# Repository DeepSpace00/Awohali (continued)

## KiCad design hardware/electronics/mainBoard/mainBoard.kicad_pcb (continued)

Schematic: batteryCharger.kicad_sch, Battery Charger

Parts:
C90, C93, C94, C98, C99: 100nF; GCM0402; Tolerance 10%; Voltage Rating 50V; MPN GRT155R71H104KE01D
C91, C92, C95, C96, C97, C100, C101, C102, C103, C104, C106, C107: 10uF; GRT1210; Tolerance 10%; Voltage Rating 25V; MPN GCM32ER71E106KA57L
C105, C108, C109: 47nF; GCM0402; Tolerance 10%; Voltage Rating 25V; MPN GRT155R71E473KE01D
C110: 4.7uF; GCM0805; Tolerance 10%; Voltage Rating 16V; MPN GRT21BR71C475KE13L
D5: PTVS13VS1UR; SOD123W; Voltage - Reverse Stabd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 13V; Voltage - Breakdown 14V4; MPN PTVS13VS1UR,115
D6, D8: ESD321DYAR; SOD523; Voltage - Reverse Stabd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 3V6; Voltage - Breakdown 4V5; MPN ESD321DYAR
D9: TPD1E05U06-Q1; SON2P65_100X60X50L50X25N; Voltage - Reverse Stabd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 5V5; Voltage - Breakdown 6V4; MPN TPD1E05U06QDPYRQ1
D15, D16: BZT52C12T-7; SOD523; Zener Voltage 12V; Forward Voltage 900mV; MPN BZT52C12T-7
D17: LTST-C191KGKT; LTST-0603; Forward Voltage 2V; MPN LTST-C191KGKT
J25: M8AS-02PFFR-SF8001; MPN M8AS-02PFFR-SF8001
J26: MUSBRM1C1M0; MUSBR-M1C1-XX; MPN MUSBRM1C1M0
J27: S2B-PH-SM4-TB; JST-PH-S2B-SM4-TB; MPN S2B-PH-SM4-TB
JP10: SolderJumper-2_P1.3mm_Bridged_RoundedPad1.0x1.5mm
L6: 2.2uH; WE-XHMI-4030; Tolerance 20%; Current Rating 7A8; MPN 74439324022
NT7, NT8: NetTie; NetTie-2_SMD_Pad2.0mm
Q1, Q3, Q4: CSD17581Q3A; SON65P300X315X90-8; MPN Texas Instruments
Q2, Q5: CSD17581Q3A; SON65P300X315X90-8; MPN CSD17581Q3A
R61: 294R; CRCW0402; Tolerance 1%; Power Rating 62m5W; MPN CRCW0402294RFKED
R62: 8K2; CRCW0402; Tolerance 1%; Power Rating 62m5W; MPN CRCW04028K20FKED
R63: 294R; CRCW0402; Tolerance 1%; Power Rating 62m5W; MPN CRCW04026K04FKED
R64, R65, R70: 5K1; CRCW0402; Tolerance 1%; Power Rating 62m5W; MPN CRCW04025K10FKED
R66: 100R; CRCW0402; Tolerance 5%; Power Rating 62m5W; MPN CRCW0402100RJNED
R67: 2K2; CRCW0402; Tolerance 1%; Power Rating 62m5W; MPN CRCW04022K20FKED
R68: 10K; CRCW0402; Tolerance 1%; Power Rating 62m5W; MPN CRCW040210K0FKED
R69: 187K; CRCW0402; Tolerance 1%; Power Rating 62m5W; MPN CRCW0402187KFKED
R71: 100K; CRCW0402; Tolerance 1%; Power Rating 62m5W; MPN CRCW0402100KFKED
R72: 29K4; CRCW0402; Tolerance 1%; Power Rating 62m5W; MPN CRCW040229K4FKED
TP77, TP78, TP80, TP81, TP83, TP85, TP86, TP88, TP89: TP_2mm; MPN N/A
TP79, TP82, TP84, TP87, TP90: RCWCTE; TP_RCW; MPN RCWCTE
U20: BQ25798; QFN40P400X400X100-29; MPN BQ25798RQMR

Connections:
+3V3: R68.1; also elsewhere on the board
/EPS Controller/BAT_CHG_INT: R68.2, U20.21 (~INT); also elsewhere on the board
/EPS Controller/Battery Charger/ACDRV1: R63.2, TP83.1, U20.11 (ACDRV1)
/EPS Controller/Battery Charger/ACDRV2: R61.2, TP85.1, U20.10 (ACDRV2)
/EPS Controller/Battery Charger/BAT: C106.1, C107.1, Q5.1, Q5.2, Q5.3, U20.22 (BAT), U20.23 (BAT)
/EPS Controller/Battery Charger/BATP: C109.1, R66.1, U20.18 (BATP)
/EPS Controller/Battery Charger/BTST1: C105.1, U20.4 (BTST1)
/EPS Controller/Battery Charger/BTST2: C108.2, U20.19 (BTST2)
/EPS Controller/Battery Charger/CC1: J26.A5 (CC1), R64.1
/EPS Controller/Battery Charger/CC2: J26.B5 (CC2), R65.1
/EPS Controller/Battery Charger/ILIM_HZ: R69.2, R71.1, U20.17 (ILIM_HZ)
/EPS Controller/Battery Charger/PMID: C94.1, C95.1, C96.1, C97.1, U20.29 (PMID)
/EPS Controller/Battery Charger/PROG: R62.1, U20.20 (PROG)
/EPS Controller/Battery Charger/PVIN: C90.1, D5.1, J25.1 (VDD), Q1.5, Q1.6, Q1.7, Q1.8, Q1.9, TP89.1, U20.8 (VAC2)
/EPS Controller/Battery Charger/REGN: C110.1, JP10.1, R69.1, R70.1, U20.5 (REGN)
/EPS Controller/Battery Charger/SDRV: Q5.4, U20.24 (SDRV)
/EPS Controller/Battery Charger/SW1: C105.2, L6.1, U20.28 (SW1)
/EPS Controller/Battery Charger/SW2: C108.1, L6.2, U20.26 (SW2)
/EPS Controller/Battery Charger/VCHG: C91.1, C92.1, C93.1, Q2.5, Q2.6, Q2.7, Q2.8, Q2.9, Q4.5, Q4.6, Q4.7, Q4.8, Q4.9, TP81.1, U20.2 (VBUS), U20.3 (VBUS)
/EPS Controller/TS: J27.1, R70.2, R72.1, U20.16 (TS); also elsewhere on the board
/EPS Controller/USB_FS.DN: D8.1, J26.A7 (D1-), J26.B7 (D2-), TP88.1; also elsewhere on the board
/EPS Controller/USB_FS.DP: D6.1, J26.A6 (D1+), J26.B6 (D2+), TP86.1; also elsewhere on the board
/EPS Controller/~CE: U20.13 (~CE); also elsewhere on the board
/EPS Controller/~QON: U20.12 (~QON); also elsewhere on the board
/EPS.SCL: U20.14 (SCL); also elsewhere on the board
/EPS.SDA: U20.15 (SDA); also elsewhere on the board
AGND: C90.2, C98.2, J27.2, NT7.2, R62.2, R71.2, R72.2, TP84.1; also elsewhere on the board
CHG+: Q5.5, Q5.6, Q5.7, Q5.8, Q5.9, R66.2, TP80.1; also elsewhere on the board
CHG-: C106.2, C107.2, TP87.1; also elsewhere on the board
GND: C91.2, C92.2, C93.2, C94.2, C95.2, C96.2, C97.2, C99.2, C100.2, C101.2, C102.2, C103.2, C104.2, C109.2, C110.2, D5.2, D6.2, D8.2, D9.2, J25.2 (VSS), J25.S1 (SHIELD), J25.S2 (SHIELD), J26.A1 (GND), J26.A12 (GND), J26.B1 (GND), J26.B12 (GND), J26.G1 (GND), J26.G2 (GND), J26.G3 (GND), J26.G4 (GND), J26.G5 (GND), J26.G6 (GND), J26.S1, J26.S2, NT7.1, NT8.1, R64.2, R65.2, TP79.1, TP82.1, TP90.1, U20.27 (GND); also elsewhere on the board
unnamed: D15.1, Q1.1, Q1.2, Q1.3, Q2.1, Q2.2, Q2.3
unnamed: D15.2, Q1.4, Q2.4, R61.1
unnamed: D16.1, Q3.1, Q3.2, Q3.3, Q4.1, Q4.2, Q4.3
unnamed: D16.2, Q3.4, Q4.4, R63.1
unnamed: D17.1, R67.2
unnamed: JP10.2, R67.1
unnamed: D17.2, U20.1 (STAT)
VBUS: C98.1, D9.1, J26.A4 (VBUS), J26.A9 (VBUS), J26.B4 (VBUS), J26.B9 (VBUS), Q3.5, Q3.6, Q3.7, Q3.8, Q3.9, TP77.1, U20.9 (VAC1)
VSS: NT8.2; also elsewhere on the board
VSYS: C99.1, C100.1, C101.1, C102.1, C103.1, C104.1, TP78.1, U20.25 (SYS); also elsewhere on the board

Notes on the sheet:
Upstream Facing USB Port
VIN: 12V
VIN: 5V@3A
I2C Address: 0x6B
Pv Panel Jack
Thermistor Connector
Pull ~{QON} low to activate shutdown mode
Charge Enable: Pull ~{CE} LOW Charge Disable: Pull ~{CE} HIGH
10K NTC
Battery Charger
Prog Resistor: 6K04 - 2S @ 1500kHz 8K2 - 2S @ 750kHz 10K5 - 3S @ 1500kHz 13K7 - 3S @ 750kHz
R69 = (RTH_COLD * RTH_HOT * (1/VT1 - 1/VT5)) / (RTH_HOT * (1/VT5 - 1) - RTH_COLD * (1/VT1 - 1)) R67 = (1/VT1 - 1) / (1/R208 + 1/RTH_COLD)
V_ILIM_HIZ = 1V + 800mR * I_INDPM I_INDPM (target input current) = 4A V_ILIM_HIZ = 4200mV R66 = R167(12000mV - 4200mV)/4200mV R68 = 100K R66 ~= 187K

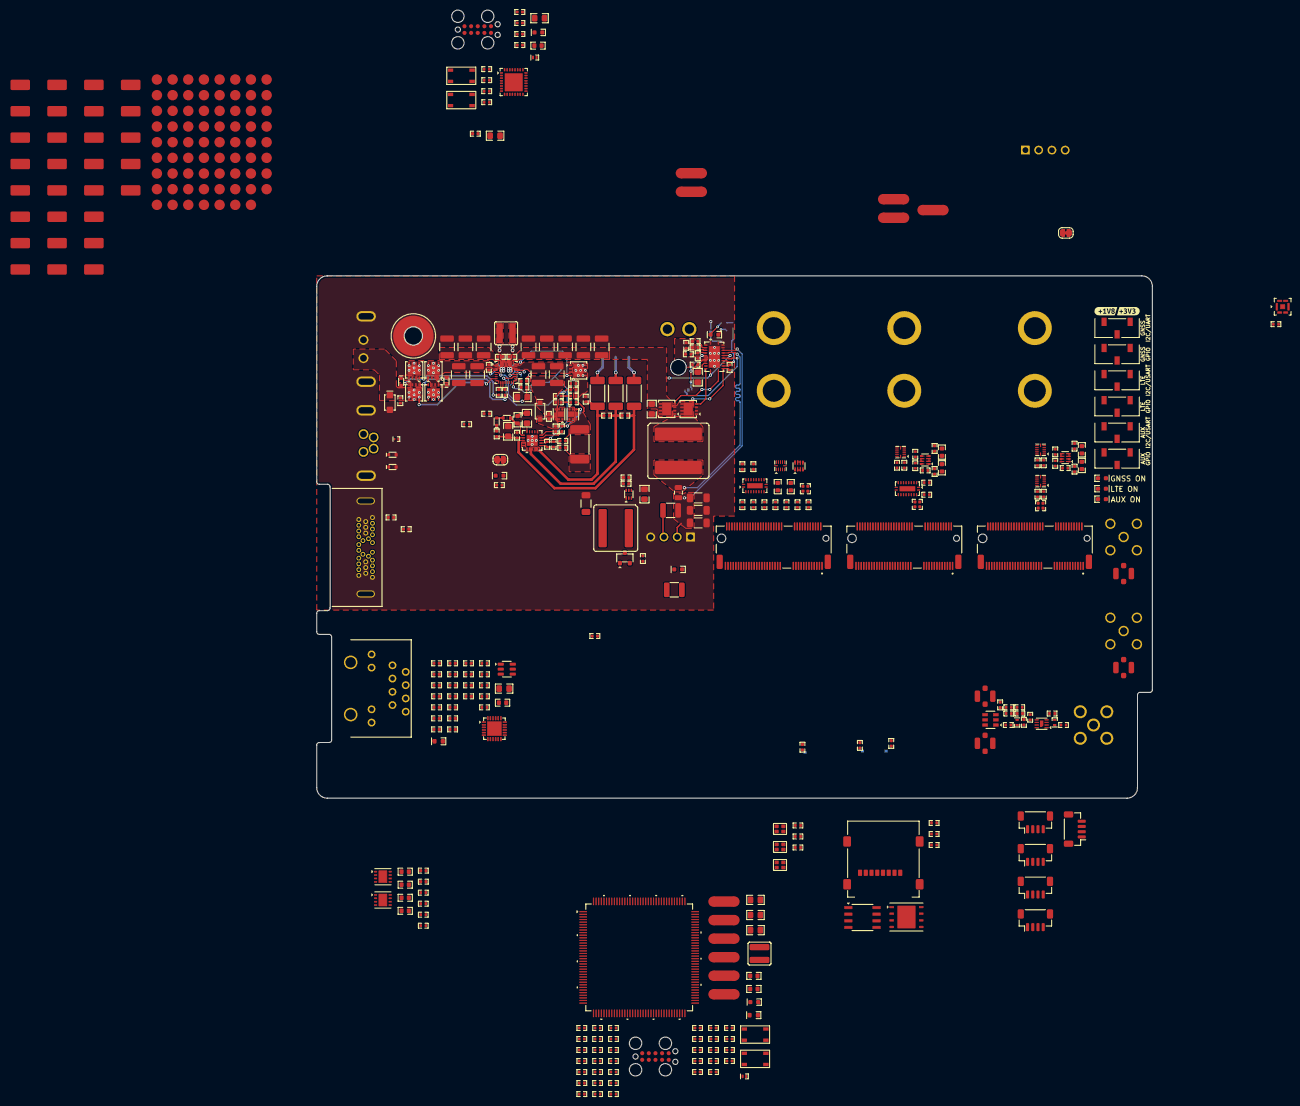
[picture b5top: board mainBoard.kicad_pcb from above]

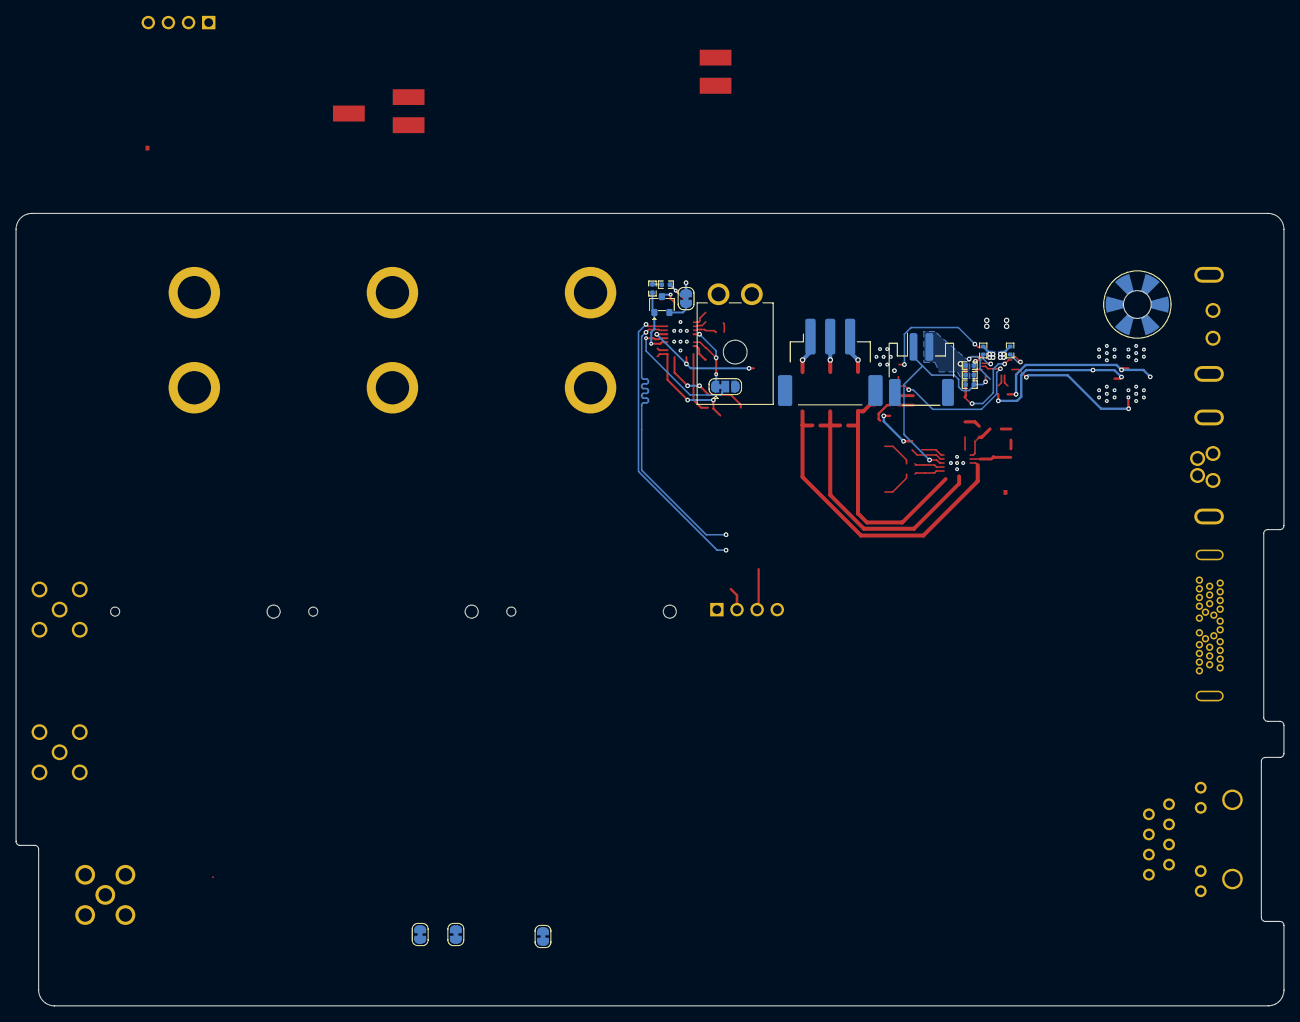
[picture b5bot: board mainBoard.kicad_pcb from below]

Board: 4 copper layers, 160.0 x 100.0 mm, 451 parts (16 on the bottom side), 272 nets.

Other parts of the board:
kibuzzard-67E082B6: G***; kibuzzard-67E082B6
kibuzzard-67E082BE: G***; kibuzzard-67E082BE

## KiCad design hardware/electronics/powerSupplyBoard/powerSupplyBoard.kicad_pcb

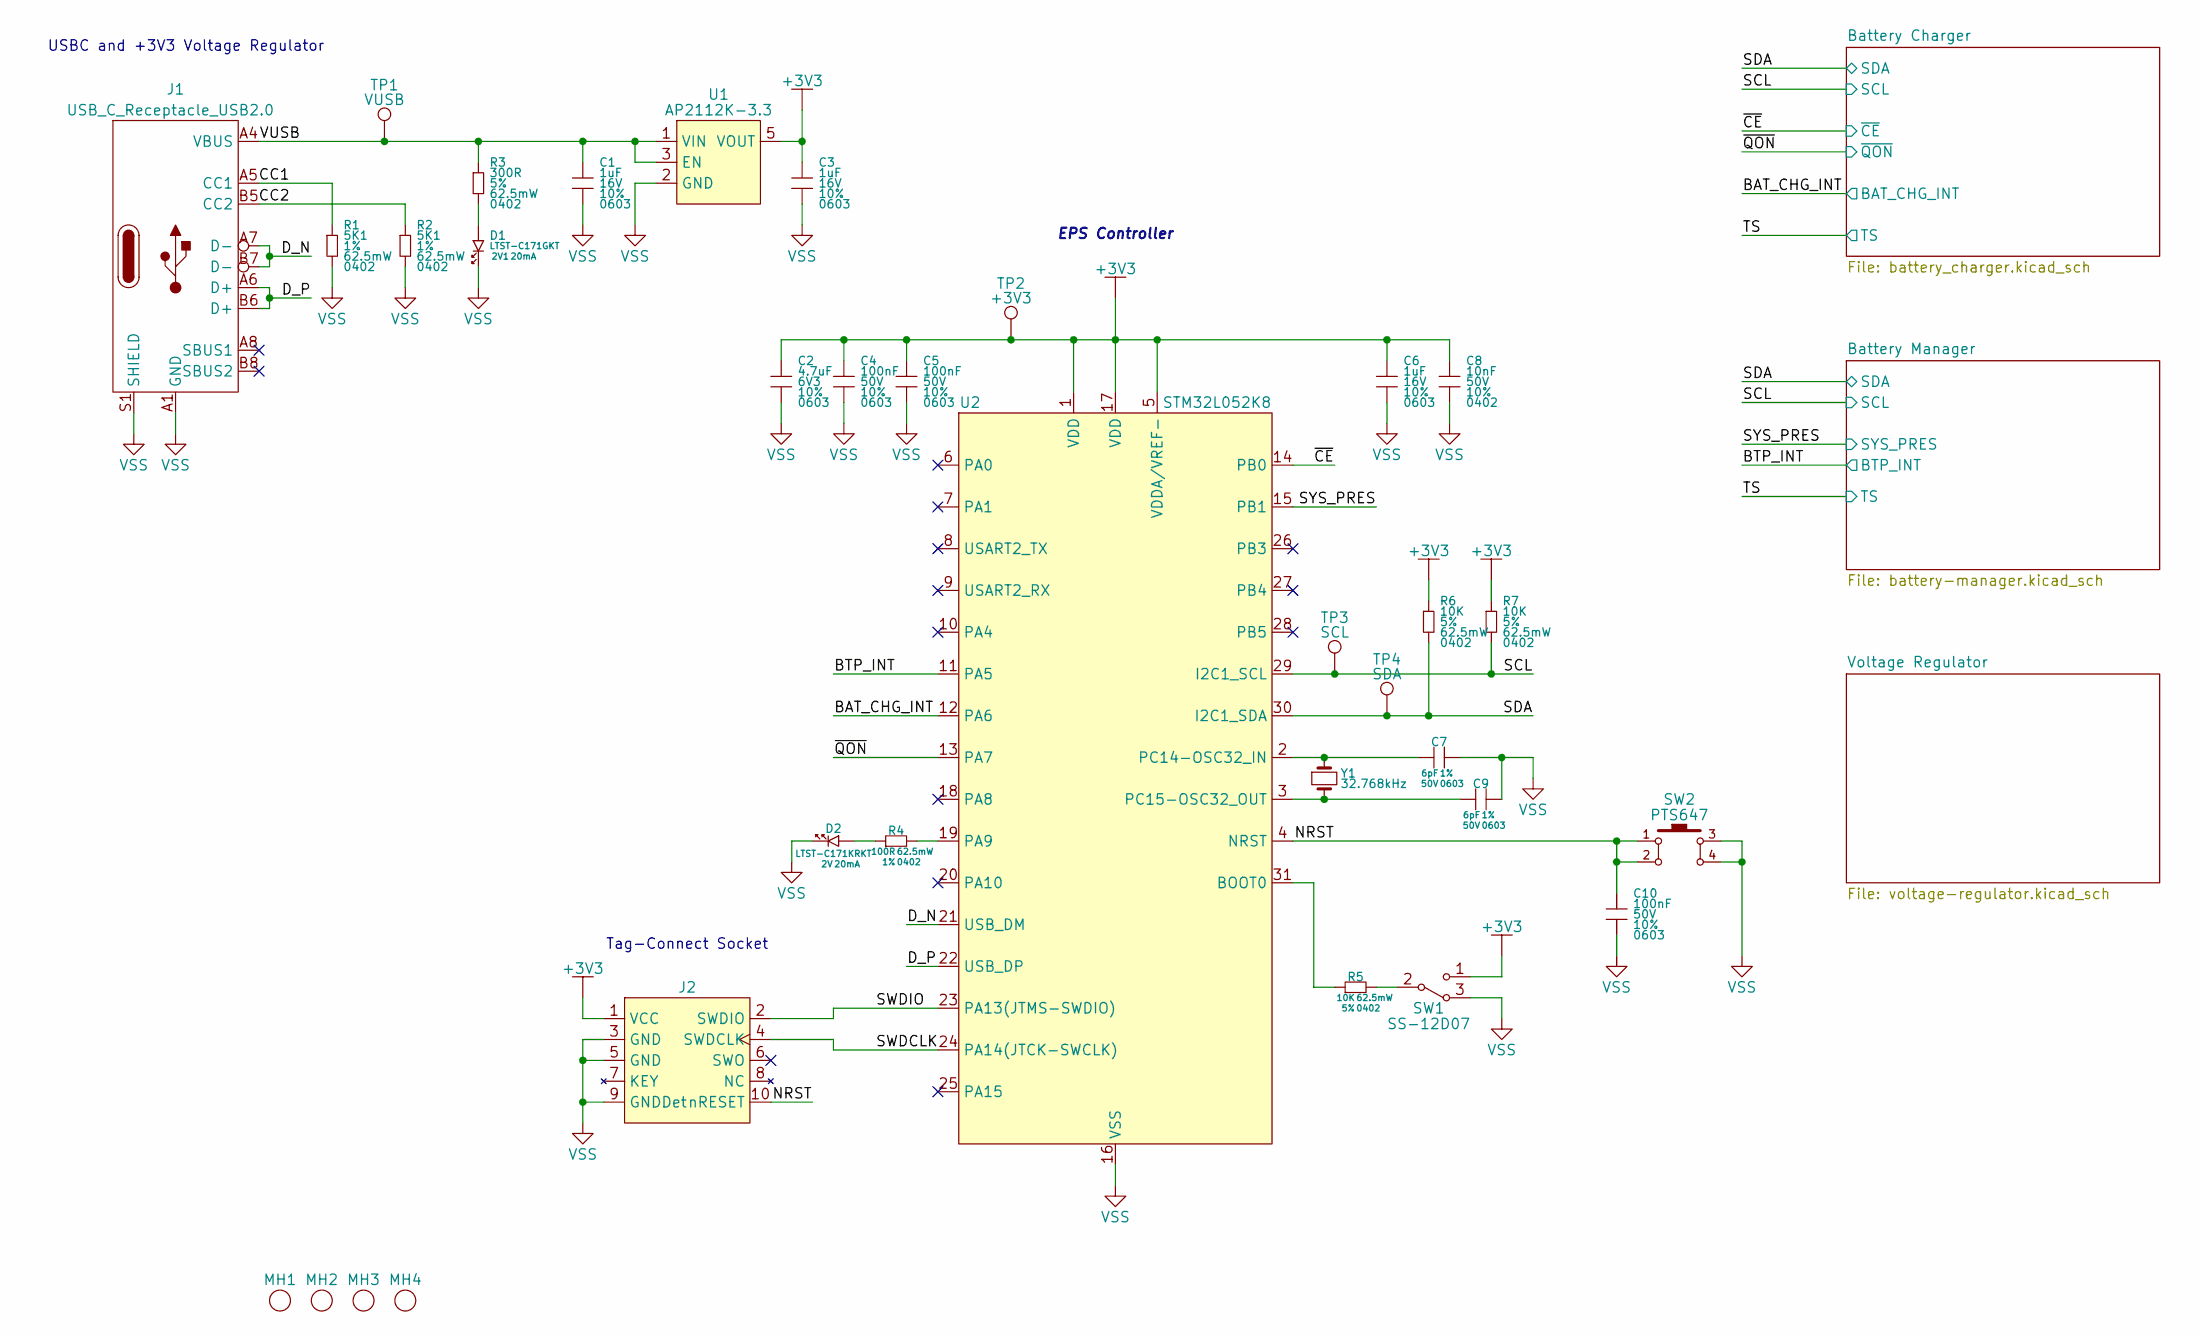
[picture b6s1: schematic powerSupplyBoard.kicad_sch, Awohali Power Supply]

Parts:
C1, C3, C6: 1uF; MLCC0603; Tolerance 10%; Voltage Rating 16V; MPN KAM15AR71C105KT
C2: 4.7uF; MLCC0603; Tolerance 10%; Voltage Rating 6V3; MPN KAM15CR70J475KT
C4, C5, C10: 100nF; MLCC0603; Tolerance 10%; Voltage Rating 50V; MPN KAM15AR71H104KM
C7, C9: 6pF; MLCC0603; Tolerace 1%; Voltage Rating 50V; MPN 06035A6R0B4T2A
C8: 10nF; MLCC0402; Tolerance 10%; Voltage Rating 50V; MPN KAM05AR71H103KH
D1: LTST-C171GKT; LTST-0805; Forward Voltage 2V1; MPN LTST-C171GKT
D2: LTST-C171KRKT; LTST-0805; Forward Voltage 2V; MPN LTST-C171KRKT
J1: USB_C_Receptacle_USB2.0; MOLEX_2171790001
J2: TC2050-FP; MPN N/A
MH1, MH2, MH3, MH4: M3_NPTH
R1, R2: 5K1; CRCW0402; Tolerance 1%; Power Rating 62.5mW; MPN CRCW04025K10FKED
R3: 300R; CRCW0402; Tolerance 5%; Power Rating 62.5mW; MPN CRCW0402300RJNED
R4: 100R; CRCW0402; Tolerance 1%; Power Rating 62.5mW; MPN CRCW0402100RFKED
R5, R6, R7: 10K; CRCW0402; Tolerance 5%; Power Rating 62.5mW; MPN CRCW040210K0JNED
SW1: SS-12D07; SS-12D07-VG_GA_PA; MPN SS-12D07-VG 4 NS GA PA
SW2: PTS647; SW_4.5x4.5; MPN PTS 647 SK38 SMTR2 LFS
TP1: VUSB; TP_1mm
TP2: +3V3; TP_1mm
TP3: SCL; TP_1mm
TP4: SDA; TP_1mm
U1: AP2112K-3.3; SOT23-5P95_280X300X110L40X38N; MPN AP2112K-3.3TRG1
U2: STM32L052K8; UFQFPN32; MPN STM32L052K8U6TR
Y1: ECS-327ATQMV; EXC-34Q; MPN ECS-.327-6-34QS-TR

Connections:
+3V3: C2.1, C3.1, C4.1, C5.1, C6.1, C8.1, J2.1 (VCC), R6.1, R7.1, SW1.1, TP2.1, U1.5 (VOUT), U2.1 (VDD), U2.5 (VDDA/VREF-), U2.17 (VDD); also elsewhere on the board
/BAT_CHG_INT: U2.12 (PA6); also elsewhere on the board
/BTP_INT: U2.11 (PA5); also elsewhere on the board
/CC1: J1.A5 (CC1), R1.1
/CC2: J1.B5 (CC2), R2.1
/D_N: J1.A7 (D-), J1.B7 (D-), U2.21 (USB_DM)
/D_P: J1.A6 (D+), J1.B6 (D+), U2.22 (USB_DP)
/NRST: C10.1, J2.10 (nRESET), SW2.1, SW2.2, U2.4 (NRST)
/SCL: R7.2, TP3.1, U2.29 (I2C1_SCL); also elsewhere on the board
/SDA: R6.2, TP4.1, U2.30 (I2C1_SDA); also elsewhere on the board
/SWDCLK: J2.4 (SWDCLK), U2.24 (PA14(JTCK-SWCLK))
/SWDIO: J2.2 (SWDIO), U2.23 (PA13(JTMS-SWDIO))
/SYS_PRES: U2.15 (PB1); also elsewhere on the board
/VUSB: C1.1, J1.A4 (VBUS), J1.A9 (VBUS), J1.B4 (VBUS), J1.B9 (VBUS), R3.1, TP1.1, U1.1 (VIN), U1.3 (EN)
/~CE: U2.14 (PB0); also elsewhere on the board
/~QON: U2.13 (PA7); also elsewhere on the board
unnamed: D1.1, R3.2
unnamed: D2.1, R4.1
unnamed: R5.2, SW1.2
unnamed: R5.1, U2.31 (BOOT0)
unnamed: R4.2, U2.19 (PA9)
unnamed: C7.1, U2.2 (PC14-OSC32_IN), Y1.1
unnamed: C9.1, U2.3 (PC15-OSC32_OUT), Y1.2
VSS: C1.2, C2.2, C3.2, C4.2, C5.2, C6.2, C7.2, C8.2, C9.2, C10.2, D1.2, D2.2, J1.A1 (GND), J1.A12 (GND), J1.B1 (GND), J1.B12 (GND), J1.S1 (SHIELD), J2.3 (GND), J2.5 (GND), J2.9 (GNDDet), R1.2, R2.2, SW1.3, SW2.3, SW2.4, U1.2 (GND), U2.16 (VSS), U2.32 (VSS), U2.33 (VSS); also elsewhere on the board

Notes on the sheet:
Tag-Connect Socket
EPS Controller
USBC and +3V3 Voltage Regulator

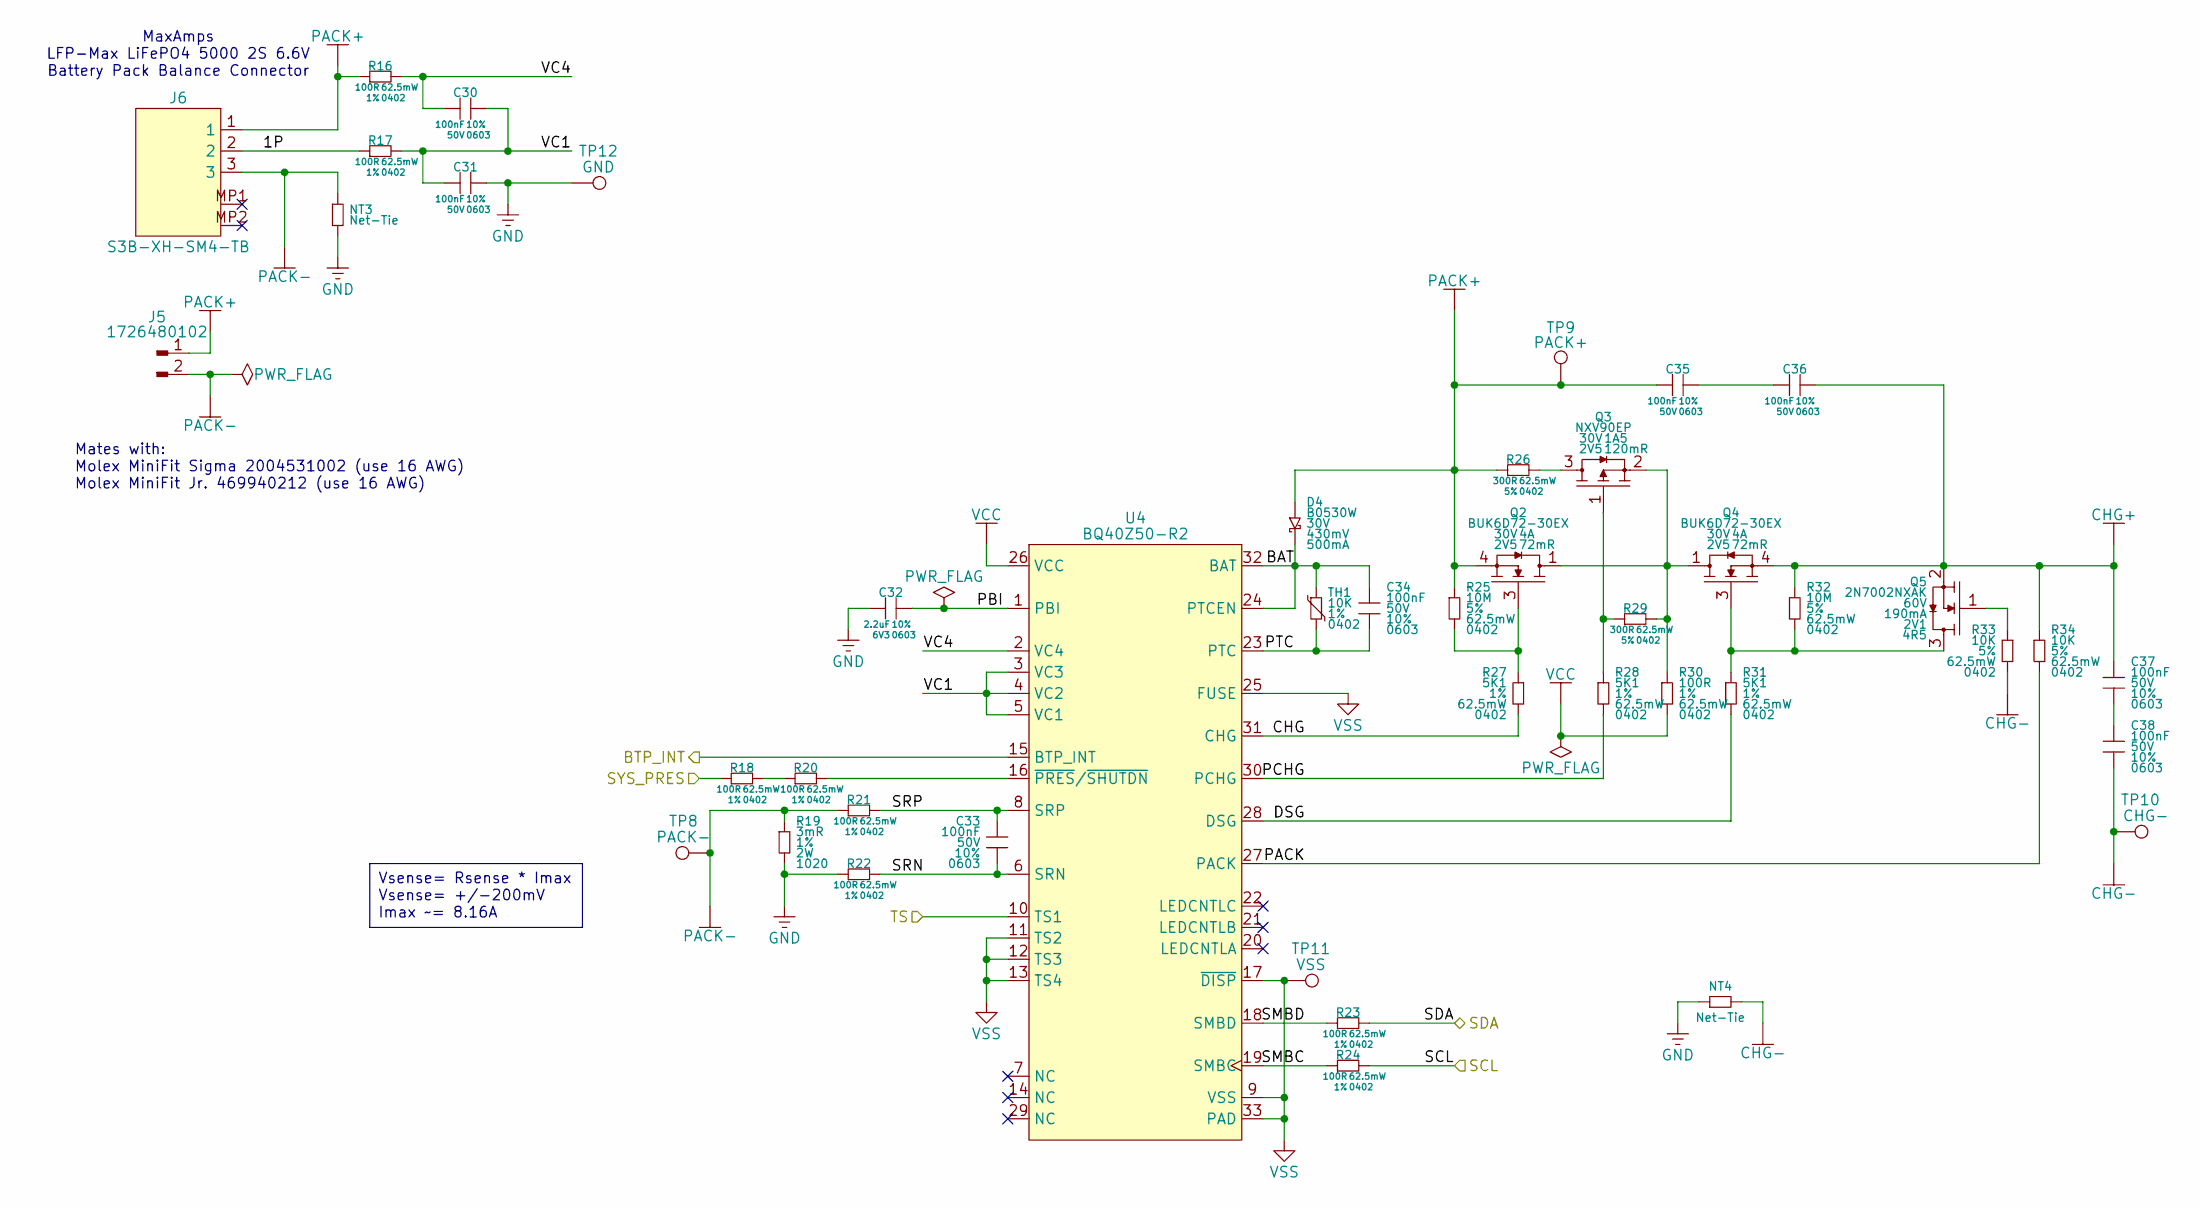
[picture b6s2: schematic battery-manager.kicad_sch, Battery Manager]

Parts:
C30, C31, C35, C36: 100nF; MLCC0603; Tolerace 10%; Voltage Rating 50V; MPN KAM15AR71H104KM
C32: 2.2uF; MLCC0603; Tolerace 10%; Voltage Rating 6V3; MPN KAM15AR70J225KT
C33, C34, C37, C38: 100nF; MLCC0603; Tolerance 10%; Voltage Rating 50V; MPN KAM15AR71H104KM
D4: B0530W; SOD123; Reverse Voltage 30V; Forward Voltage 430mV; MPN B0530W-7-F
J5: 1726480102; MPN 1726480102
J6: S3B-XH-SM4-TB; JST_XH_S3B-SM4-TB; MPN S3B-XH-SM4-TB
NT3, NT4: Net-Tie; NetTie-2_SMD_Pad2.0mm
Q2, Q4: BUK6D72-30EX; UDFN6P65_200X200X65L30X25N; MPN BUK6D72-30EX
Q3: NXV90EP; SOT23-3P95_230X290X100L43X30N; MPN NXV90EPR
Q5: 2N7002NXAK; SOT23-3P95_230X290X100L43X30N; MPN 2N7002NXAKR
R16, R17, R18, R20, R21, R22, R23, R24, R30: 100R; CRCW0402; Tolerance 1%; Power Rating 62.5mW; MPN CRCW0402100RFKED
R19: 3mR; WSL1020; Tolerance 1%; Power Rating 2W; MPN WSL10203L000FEA
R25, R32: 10M; CRCW0402; Tolerance 5%; Power Rating 62.5mW; MPN CRCW040210M0JNED
R26, R29: 300R; CRCW0402; Tolerance 5%; Power Rating 62.5mW; MPN CRCW0402300RJNED
R27, R28, R31: 5K1; CRCW0402; Tolerance 1%; Power Rating 62.5mW; MPN CRCW04025K10FKED
R33, R34: 10K; CRCW0402; Tolerance 5%; Power Rating 62.5mW; MPN CRCW040210K0JNED
TH1: 10K; SON2P65_100X60X50L50X25N; Resistance Tolerance 1%; MPN TMP6131QDECRQ1
TP8: PACK-; TP_1mm
TP9: PACK+; TP_1mm
TP10: CHG-; TP_1mm
TP11: VSS; TP_1mm
TP12: GND; TP_1mm
U4: BQ40Z50-R2; RSM0032A; MPN BQ40Z50RSMR-R2

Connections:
/BTP_INT: U4.15 (BTP_INT); also elsewhere on the board
/Battery Manager/1P: J6.2, R17.1
/Battery Manager/BAT: C34.1, D4.2, TH1.1, U4.24 (PTCEN), U4.32 (BAT)
/Battery Manager/CHG: R27.2, U4.31 (CHG)
/Battery Manager/DSG: R31.2, U4.28 (DSG)
/Battery Manager/PACK: R34.2, U4.27 (PACK)
/Battery Manager/PBI: C32.2, U4.1 (PBI)
/Battery Manager/PCHG: R28.2, U4.30 (PCHG)
/Battery Manager/PTC: C34.2, TH1.2, U4.23 (PTC)
/Battery Manager/SMBC: R24.1, U4.19 (SMBC)
/Battery Manager/SMBD: R23.1, U4.18 (SMBD)
/Battery Manager/SRN: C33.2, R22.2, U4.6 (SRN)
/Battery Manager/SRP: C33.1, R21.2, U4.8 (SRP)
/Battery Manager/VC1: C30.2, C31.1, R17.2, U4.3 (VC3), U4.4 (VC2), U4.5 (VC1)
/Battery Manager/VC4: C30.1, R16.2, U4.2 (VC4)
/SCL: R24.2; also elsewhere on the board
/SDA: R23.2; also elsewhere on the board
/SYS_PRES: R18.1; also elsewhere on the board
/TS: U4.10 (TS1); also elsewhere on the board
CHG+: C36.2, C37.1, Q4.4, Q4.8, Q5.2, R32.1, R34.1; also elsewhere on the board
CHG-: C38.2, NT4.2, R33.2, TP10.1; also elsewhere on the board
GND: C31.2, C32.1, NT3.2, NT4.1, R19.2, R22.1, TP12.1; also elsewhere on the board
unnamed: C35.2, C36.1
unnamed: C37.2, C38.1
unnamed: Q2.1, Q2.2, Q2.5, Q2.6, Q2.7, Q3.2, Q4.1, Q4.2, Q4.5, Q4.6, Q4.7, R29.2, R30.1
unnamed: Q2.3, R25.2, R27.1
unnamed: Q3.1, R28.1, R29.1
unnamed: Q3.3, R26.2
unnamed: Q4.3, Q5.3, R31.1, R32.2
unnamed: Q5.1, R33.1
unnamed: R18.2, R20.1
unnamed: R20.2, U4.16 (~PRES/~SHUTDN)
PACK+: C35.1, D4.1, J5.1, J6.1, Q2.4, Q2.8, R16.1, R25.1, R26.1, TP9.1
PACK-: J5.2, J6.3, NT3.1, R19.1, R21.1, TP8.1
VCC: R30.2, U4.26 (VCC)
VSS: TP11.1, U4.9 (VSS), U4.11 (TS2), U4.12 (TS3), U4.13 (TS4), U4.17 (~DISP), U4.25 (FUSE), U4.33 (PAD); also elsewhere on the board

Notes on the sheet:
MaxAmps LFP-Max LiFePO4 5000 2S 6.6V Battery Pack Balance Connector
Mates with: Molex MiniFit Sigma 2004531002 (use 16 AWG) Molex MiniFit Jr. 469940212 (use 16 AWG)
Vsense= Rsense * Imax Vsense= +/-200mV Imax ~= 8.16A

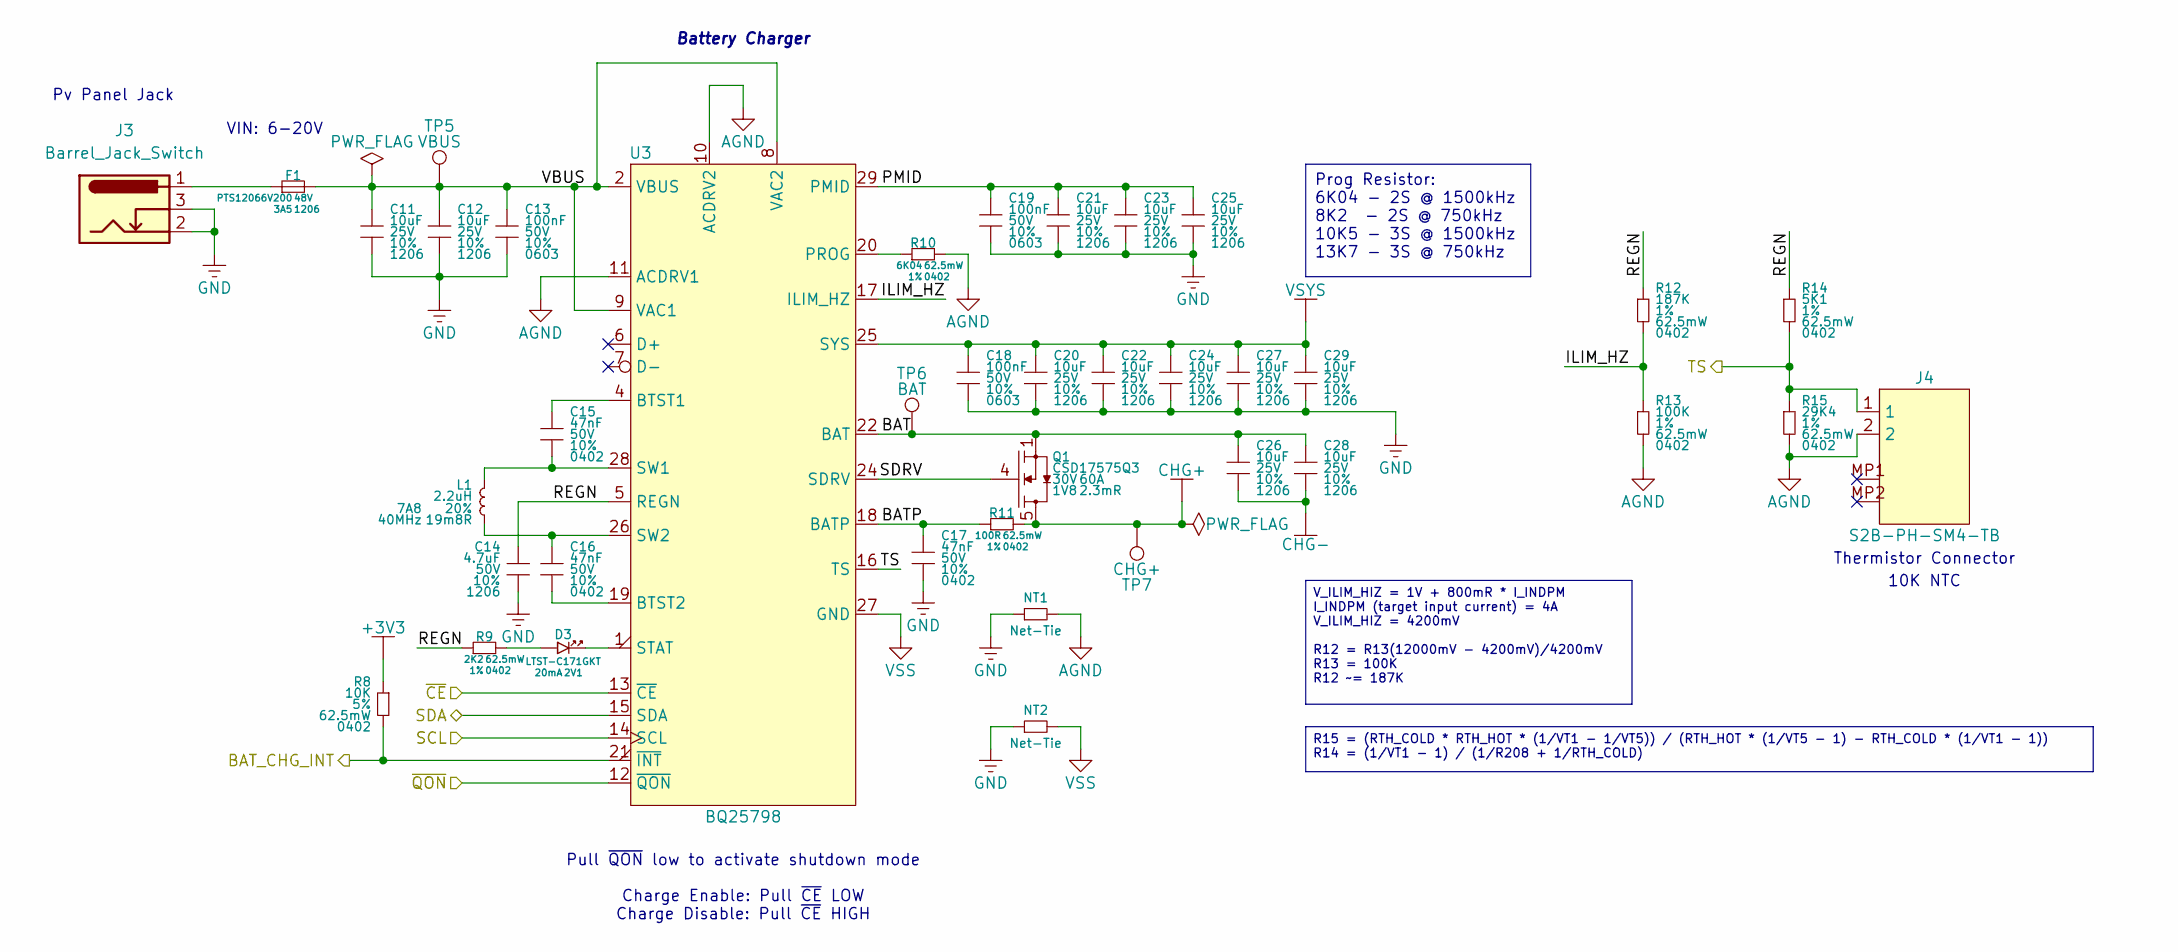
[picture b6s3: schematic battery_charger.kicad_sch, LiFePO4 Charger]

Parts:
C11, C12, C20, C21, C22, C23, C24, C25, C26, C27, C28, C29: 10uF; MLCC1206; Tolerance 10%; Voltage Rating 25V; MPN CGA5L1X7R1E106K160DC
C13, C18, C19: 100nF; MLCC0603; Tolerance 10%; Voltage Rating 50V; MPN KAM15AR71H104KM
C14: 4.7uF; MLCC1206; Tolerance 10%; Voltage Rating 50V; MPN 12065C475K4T4A
C15, C16, C17: 47nF; MLCC0402; Tolerance 10%; Voltage Rating 50V; MPN 04025C472K4T2A
D3: LTST-C171GKT; LTST-0805; Forward Voltage 2V1; MPN LTST-C171GKT
F1: PTS12066V200; PTS1206; Voltage 48V; MPN PTS12066V200
J3: Barrel_Jack_Switch; PJ-002A; MPN PJ-002A
J4: S2B-PH-SM4-TB; JST-PH-S2B-SM4-TB; MPN S2B-PH-SM4-TB
L1: 2.2uH; WE-XHMI-4030; Tolerance 20%; Current Rating 7A8; MPN 74439324022
NT1, NT2: Net-Tie; NetTie-2_SMD_Pad2.0mm
Q1: CSD17575Q3; SON8P65_330X330X100L45X34N; MPN CSD17575Q3
R8: 10K; CRCW0402; Tolerance 5%; Power Rating 62.5mW; MPN CRCW040210K0JNED
R9: 2K2; CRCW0402; Tolerance 1%; Power Rating 62.5mW; MPN CRCW04022K20FKED
R10: 6K04; CRCW0402; Tolerance 1%; Power Rating 62.5mW; MPN CRCW04026K04FKED
R11: 100R; CRCW0402; Tolerance 1%; Power Rating 62.5mW; MPN CRCW0402100RFKED
R12: 187K; CRCW0402; Tolerance 1%; Power Rating 62.5mW; MPN CRCW0402187KFKED
R13: 100K; CRCW0402; Tolerance 1%; Power Rating 62.5mW; MPN CRCW0402100KFKED
R14: 5K1; CRCW0402; Tolerance 1%; Power Rating 62.5mW; MPN CRCW04025K10FKED
R15: 29K4; CRCW0402; Tolerance 1%; Power Rating 62.5mW; MPN CRCW040229K4FKED
TP5: VBUS; TP_1mm
TP6: BAT; TP_1mm
TP7: CHG+; TP_1mm
U3: BQ25798; RQM0029A; MPN BQ25798

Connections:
+3V3: R8.1; also elsewhere on the board
/BAT_CHG_INT: R8.2, U3.21 (~INT); also elsewhere on the board
/Battery Charger/BAT: C26.1, C28.1, Q1.1, Q1.2, Q1.3, TP6.1, U3.22 (BAT), U3.23 (BAT)
/Battery Charger/BATP: C17.1, R11.1, U3.18 (BATP)
/Battery Charger/ILIM_HZ: R12.2, R13.1, U3.17 (ILIM_HZ)
/Battery Charger/PMID: C19.1, C21.1, C23.1, C25.1, U3.29 (PMID)
/Battery Charger/REGN: C14.1, R9.1, R12.1, R14.1, U3.5 (REGN)
/Battery Charger/SDRV: Q1.4, U3.24 (SDRV)
/SCL: U3.14 (SCL); also elsewhere on the board
/SDA: U3.15 (SDA); also elsewhere on the board
/TS: J4.1, R14.2, R15.1, U3.16 (TS); also elsewhere on the board
/~CE: U3.13 (~CE); also elsewhere on the board
/~QON: U3.12 (~QON); also elsewhere on the board
AGND: J4.2, NT1.2, R10.2, R13.2, R15.2, U3.10 (ACDRV2), U3.11 (ACDRV1)
CHG+: Q1.5, Q1.6, Q1.7, Q1.8, R11.2, TP7.1; also elsewhere on the board
CHG-: C26.2, C28.2; also elsewhere on the board
GND: C11.2, C12.2, C13.2, C14.2, C17.2, C18.2, C19.2, C20.2, C21.2, C22.2, C23.2, C24.2, C25.2, C27.2, C29.2, J3.2, J3.3, NT1.1, NT2.1; also elsewhere on the board
unnamed: D3.1, R9.2
unnamed: F1.1, J3.1
unnamed: C15.1, U3.4 (BTST1)
unnamed: C16.2, U3.19 (BTST2)
unnamed: R10.1, U3.20 (PROG)
unnamed: D3.2, U3.1 (STAT)
unnamed: C15.2, L1.1, U3.28 (SW1)
unnamed: C16.1, L1.2, U3.26 (SW2)
VBUS: C11.1, C12.1, C13.1, F1.2, TP5.1, U3.2 (VBUS), U3.3 (VBUS), U3.8 (VAC2), U3.9 (VAC1)
VSS: NT2.2, U3.27 (GND); also elsewhere on the board
VSYS: C18.1, C20.1, C22.1, C24.1, C27.1, C29.1, U3.25 (SYS); also elsewhere on the board

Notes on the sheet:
Pv Panel Jack
VIN: 6-20V
Battery Charger
10K NTC
Charge Enable: Pull ~{CE} LOW Charge Disable: Pull ~{CE} HIGH
Pull ~{QON} low to activate shutdown mode
Thermistor Connector
V_ILIM_HIZ = 1V + 800mR * I_INDPM I_INDPM (target input current) = 4A V_ILIM_HIZ = 4200mV R12 = R13(12000mV - 4200mV)/4200mV R13 = 100K R12 ~= 187K
Prog Resistor: 6K04 - 2S @ 1500kHz 8K2 - 2S @ 750kHz 10K5 - 3S @ 1500kHz 13K7 - 3S @ 750kHz
R15 = (RTH_COLD * RTH_HOT * (1/VT1 - 1/VT5)) / (RTH_HOT * (1/VT5 - 1) - RTH_COLD * (1/VT1 - 1)) R14 = (1/VT1 - 1) / (1/R208 + 1/RTH_COLD)

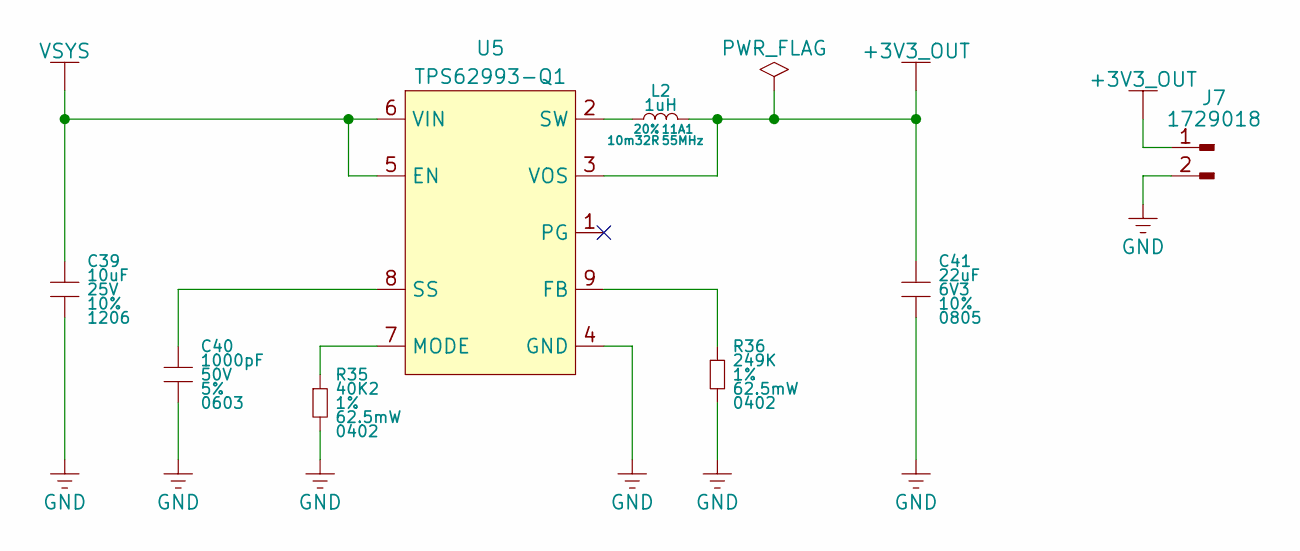
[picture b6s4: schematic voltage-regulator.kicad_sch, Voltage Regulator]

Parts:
C39: 10uF; MLCC1206; Tolerance 10%; Voltage Rating 25V; MPN CGA5L1X7R1E106K160DC
C40: 1000pF; MLCC0603; Tolerance 5%; Voltage Rating 50V; MPN KAM15AR71H102JT
C41: 22uF; MLCC0805; Tolerance 10%; Voltage Rating 6V3; MPN KAM21AT70J226KU
J7: 1729018; 5mmTerminalBlock; MPN 1729018
L2: 1uH; WE-XHMI-4030; Tolerance 20%; Current Rating 11A1; MPN 74439324010
R35: 40K2; CRCW0402; Tolerance 1%; Power Rating 62.5mW; MPN CRCW040240K2FKED
R36: 249K; CRCW0402; Tolerance 1%; Power Rating 62.5mW; MPN CRCW0402249KFKED
U5: TPS62993-Q1; RYT0009A; MPN TPS62993QRYTRQ1

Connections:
+3V3_OUT: C41.1, J7.1, L2.2, U5.3 (VOS)
GND: C39.2, C40.2, C41.2, J7.2, R35.2, R36.2, U5.4 (GND); also elsewhere on the board
unnamed: R36.1, U5.9 (FB)
unnamed: R35.1, U5.7 (MODE)
unnamed: C40.1, U5.8 (SS)
unnamed: L2.1, U5.2 (SW)
VSYS: C39.1, U5.5 (EN), U5.6 (VIN); also elsewhere on the board
